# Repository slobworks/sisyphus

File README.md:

DISCLAIMER: I have not had a chance to test this out myself. I don't have any idea how or where to get an I/O bracket that would fit this consequently; I tried to make it match the one used by an ISA SB16 sound card I had on hand, but it probably is incorrect. Feel free to edit it as you see fit, in fact you have my blessing to do so.

This is the low cost (LC) variant of Sisyphus. The board is close to 1/2 the size, the headphone amp + slider and all but one 3.5" jack (the Line Output) has been removed. It still has internal Line In through a 4-pin, CD-ROM cable header, to allow for daisy-chaining sound cards within the computer.

Made in KiCAD 8.0something.
Also includes gerber files so you can try it out for yourself.

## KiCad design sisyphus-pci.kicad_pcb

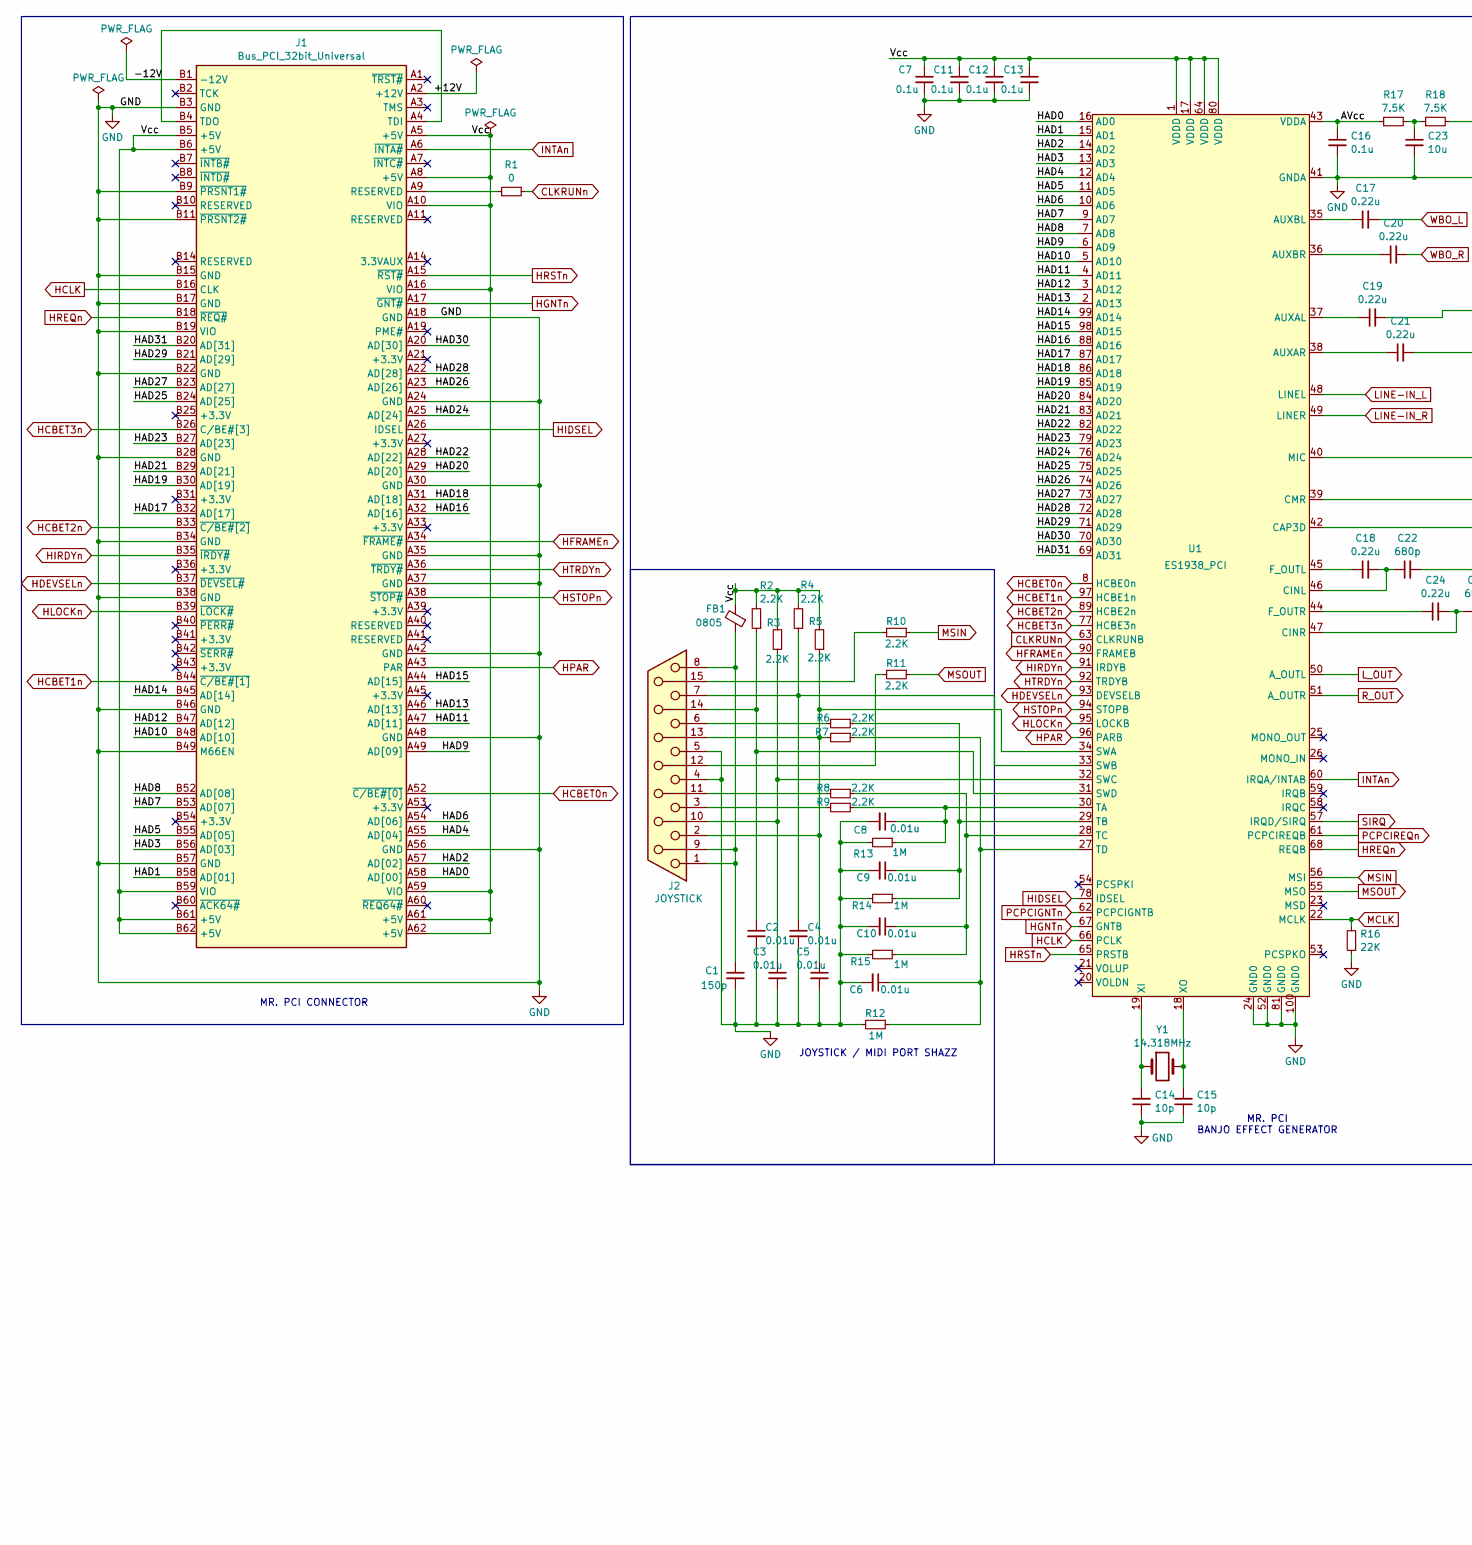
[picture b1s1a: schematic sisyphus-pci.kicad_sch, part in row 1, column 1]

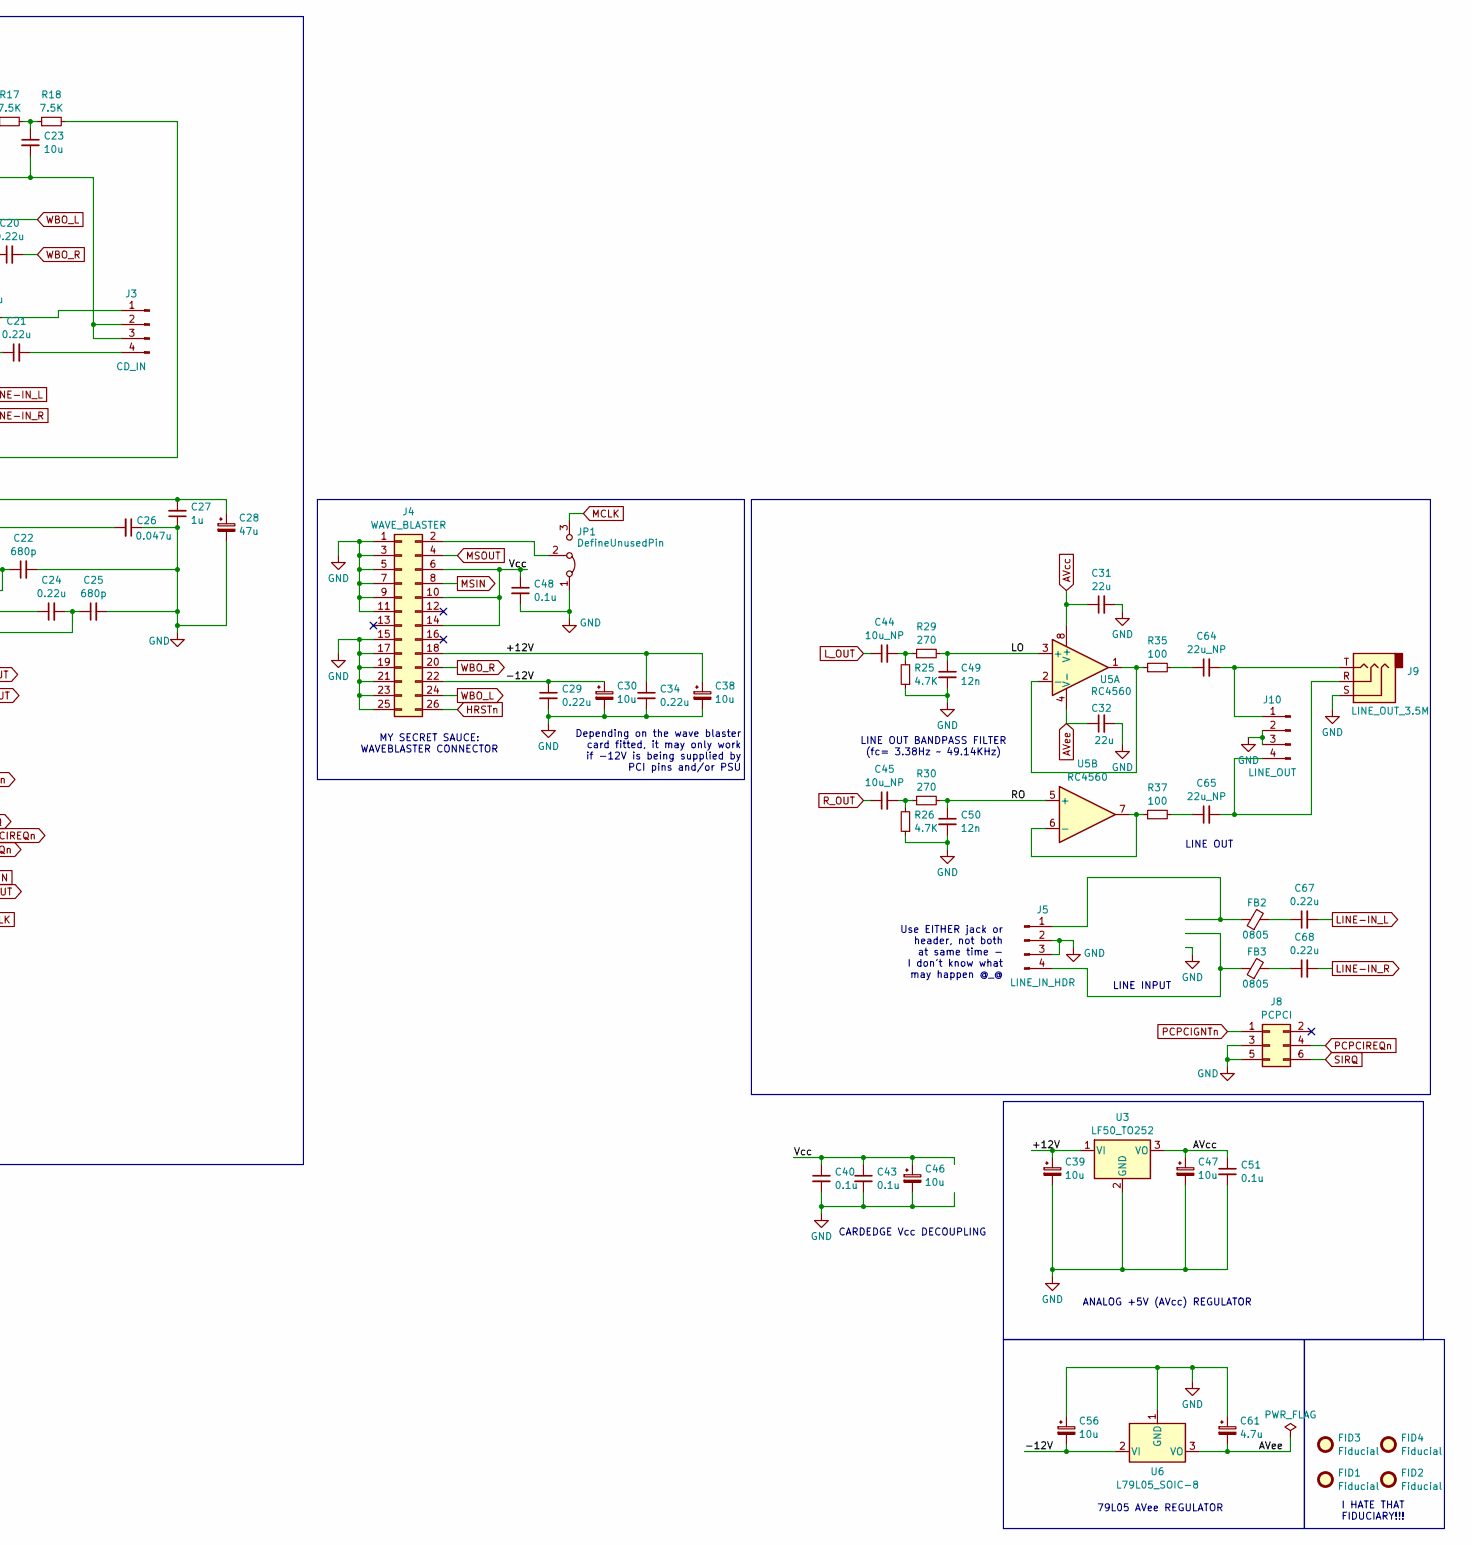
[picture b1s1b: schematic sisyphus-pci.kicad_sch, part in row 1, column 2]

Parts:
C1: 150p; C_0805_2012Metric
C2, C3, C4, C5, C6, C8, C9, C10: 0.01u; C_0805_2012Metric
C7, C11, C12, C13, C16, C40, C43, C48, C51: 0.1u; C_0805_2012Metric
C14, C15: 10p; C_0805_2012Metric
C17, C18, C19, C20, C21, C24, C29, C34, C67, C68: 0.22u; C_0805_2012Metric
C22, C25: 680p; C_0805_2012Metric
C23, C30, C38, C46, C56: 10u; C_1206_3216Metric
C26: 0.047u; C_0805_2012Metric
C27: 1u; C_0805_2012Metric
C28: 47u; C_1210_3225Metric
C31, C32: 22u; C_1206_3216Metric
C39, C47: 10u; CP_Elec_5x5.3
C44, C45: 10u_NP; CP_Radial_D5.0mm_P2.00mm
C49, C50: 12n; C_0805_2012Metric
C61: 4.7u; CP_Elec_5x5.3
C64, C65: 22u_NP; CP_Radial_D5.0mm_P2.00mm
FB1, FB2, FB3: 0805; L_0805_2012Metric
FID1, FID2, FID3, FID4: Fiducial; Fiducial_0.5mm_Mask1mm
J1: Bus_PCI_32bit_Universal; BUS_PCI
J2: JOYSTICK; DSUB-15_Female_Horizontal_P2.77x2.84mm_EdgePinOffset7.70mm_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
J3: CD_IN; PinHeader_1x04_P2.54mm_Vertical
J4: WAVE_BLASTER; PinHeader_2x13_P2.54mm_Vertical
J5: LINE_IN_HDR; PinHeader_1x04_P2.54mm_Vertical
J8: PCPCI; PinHeader_2x03_P2.54mm_Vertical
J9: LINE_OUT_3.5M; Jack_3.5mm_CUI_SJ1-3523N_Horizontal
J10: LINE_OUT; PinHeader_1x04_P2.54mm_Vertical
JP1: DefineUnusedPin; PinHeader_1x03_P1.27mm_Vertical
R1: 0; R_0805_2012Metric
R2, R3, R4, R5, R6, R7, R8, R9, R10, R11: 2.2K; R_0805_2012Metric
R12, R13, R14, R15: 1M; R_0805_2012Metric
R16: 22K; R_0805_2012Metric
R17, R18: 7.5K; R_0805_2012Metric
R25, R26: 4.7K; R_0805_2012Metric
R29, R30: 270; R_0805_2012Metric
R35, R37: 100; R_0805_2012Metric
U1: ES1938_PCI; TQFP-100_12x12mm_P0.4mm
U3: LF50_TO252; TO-252-2
U5: RC4560; SOIC-8_DMP-8
U6: L79L05_SOIC-8; SOIC-8_3.9x4.9mm_P1.27mm
Y1: 14.318MHz; Crystal_SMD_FOX_FE-2Pin_7.5x5.0mm_HandSoldering

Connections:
/+12V: C34.1, C38.1, C39.1, J1.A2 (+12V), J4.18, U3.1 (VI)
/-12V: C29.1, C30.1, C56.2, J1.B1 (-12V), J4.22, U6.2 (VI)
/HAD0: J1.A58 (AD[00]), U1.16 (AD0)
/HAD1: J1.B58 (AD[01]), U1.15 (AD1)
/HAD2: J1.A57 (AD[02]), U1.14 (AD2)
/HAD3: J1.B56 (AD[03]), U1.13 (AD3)
/HAD4: J1.A55 (AD[04]), U1.12 (AD4)
/HAD5: J1.B55 (AD[05]), U1.11 (AD5)
/HAD6: J1.A54 (AD[06]), U1.10 (AD6)
/HAD7: J1.B53 (AD[07]), U1.9 (AD7)
/HAD8: J1.B52 (AD[08]), U1.7 (AD8)
/HAD9: J1.A49 (AD[09]), U1.6 (AD9)
/HAD10: J1.B48 (AD[10]), U1.5 (AD10)
/HAD11: J1.A47 (AD[11]), U1.4 (AD11)
/HAD12: J1.B47 (AD[12]), U1.3 (AD12)
/HAD13: J1.A46 (AD[13]), U1.2 (AD13)
/HAD14: J1.B45 (AD[14]), U1.99 (AD14)
/HAD15: J1.A44 (AD[15]), U1.98 (AD15)
/HAD16: J1.A32 (AD[16]), U1.88 (AD16)
/HAD17: J1.B32 (AD[17]), U1.87 (AD17)
/HAD18: J1.A31 (AD[18]), U1.86 (AD18)
/HAD19: J1.B30 (AD[19]), U1.85 (AD19)
/HAD20: J1.A29 (AD[20]), U1.84 (AD20)
/HAD21: J1.B29 (AD[21]), U1.83 (AD21)
/HAD22: J1.A28 (AD[22]), U1.82 (AD22)
/HAD23: J1.B27 (AD[23]), U1.79 (AD23)
/HAD24: J1.A25 (AD[24]), U1.76 (AD24)
/HAD25: J1.B24 (AD[25]), U1.75 (AD25)
/HAD26: J1.A23 (AD[26]), U1.74 (AD26)
/HAD27: J1.B23 (AD[27]), U1.73 (AD27)
/HAD28: J1.A22 (AD[28]), U1.72 (AD28)
/HAD29: J1.B21 (AD[29]), U1.71 (AD29)
/HAD30: J1.A20 (AD[30]), U1.70 (AD30)
/HAD31: J1.B20 (AD[31]), U1.69 (AD31)
/LO: C49.1, R29.2, U5.3 (+)
/RO: C50.1, R30.2, U5.5 (+)
/Vcc: C7.1, C11.1, C12.1, C13.1, C40.1, C43.1, C46.1, C48.1, FB1.2, J1.A5 (+5V), J1.A8 (+5V), J1.A10 (VIO), J1.A16 (VIO), J1.A59 (VIO), J1.A61 (+5V), J1.A62 (+5V), J1.B5 (+5V), J1.B6 (+5V), J1.B59 (VIO), J1.B61 (+5V), J1.B62 (+5V), J4.6, J4.10, J4.14, R2.2, R3.2, R4.2, R5.2, U1.1 (VDDD), U1.17 (VDDD), U1.64 (VDDD), U1.80 (VDDD)
AVcc: C16.1, C31.1, C47.1, C51.1, R17.1, U1.43 (VDDA), U3.3 (VO), U5.8 (V+)
AVee: C32.1, C61.2, U5.4 (V-), U6.3 (VO)
CLKRUNn: R1.2, U1.63 (CLKRUNB)
GND: C1.2, C2.2, C3.2, C4.2, C5.2, C6.2, C7.2, C8.2, C9.2, C10.2, C11.2, C12.2, C13.2, C14.1, C15.1, C16.2, C22.2, C23.2, C25.2, C26.1, C27.1, C28.2, C29.2, C30.2, C31.2, C32.2, C34.2, C38.2, C39.2, C40.2, C43.2, C46.2, C47.2, C48.2, C49.2, C50.2, C51.2, C56.1, C61.1, J1.A18 (GND), J1.A24 (GND), J1.A30 (GND), J1.A35 (GND), J1.A37 (GND), J1.A42 (GND), J1.A48 (GND), J1.A56 (GND), J1.B3 (GND), J1.B9 (~PRSNT1#), J1.B11 (~PRSNT2#), J1.B15 (GND), J1.B17 (GND), J1.B19 (VIO), J1.B22 (GND), J1.B28 (GND), J1.B34 (GND), J1.B38 (GND), J1.B46 (GND), J1.B49 (M66EN), J1.B57 (GND), J2.4, J2.5, J3.2, J3.3, J4.1, J4.3, J4.5, J4.7, J4.9, J4.11, J4.15, J4.17, J4.19, J4.21, J4.23, J4.25, J5.2, J5.3, J8.3, J8.5, J9.S, J10.2, J10.3, JP1.1 (A), R12.2, R13.2, R14.2, R15.2, R16.1, R25.1, R26.1, U1.24 (GND0), U1.41 (GNDA), U1.52 (GND0), U1.81 (GND0), U1.100 (GND0), U3.2 (GND), U6.1 (GND)
HCBET0n: J1.A52 (~C/BE#[0]), U1.8 (HCBE0n)
HCBET1n: J1.B44 (~C/BE#[1]), U1.97 (HCBE1n)
HCBET2n: J1.B33 (~C/BE#[2]), U1.89 (HCBE2n)
HCBET3n: J1.B26 (C/BE#[3]), U1.77 (HCBE3n)
HCLK: J1.B16 (CLK), U1.66 (PCLK)
HDEVSELn: J1.B37 (~DEVSEL#), U1.93 (DEVSELB)
HFRAMEn: J1.A34 (~FRAME#), U1.90 (FRAMEB)
HGNTn: J1.A17 (~GNT#), U1.67 (GNTB)
HIDSEL: J1.A26 (IDSEL), U1.78 (IDSEL)
HIRDYn: J1.B35 (~IRDY#), U1.91 (IRDYB)
HLOCKn: J1.B39 (~LOCK#), U1.95 (LOCKB)
HPAR: J1.A43 (PAR), U1.96 (PARB)
HREQn: J1.B18 (~REQ#), U1.68 (REQB)
HRSTn: J1.A15 (~RST#), J4.26, U1.65 (PRSTB)
HSTOPn: J1.A38 (~STOP#), U1.94 (STOPB)
HTRDYn: J1.A36 (~TRDY#), U1.92 (TRDYB)
INTAn: J1.A6 (~INTA#), U1.60 (IRQA/INTAB)
LINE-IN_L: C67.2, U1.48 (LINEL)
LINE-IN_R: C68.2, U1.49 (LINER)
L_OUT: C44.1, U1.50 (A_OUTL)
MCLK: JP1.3 (B), R16.2, U1.22 (MCLK)
MSIN: J4.8, R10.1, U1.56 (MSI)
MSOUT: J4.4, R11.1, U1.55 (MSO)
unnamed: C23.1, R17.2, R18.1
unnamed: C44.2, R25.2, R29.1
unnamed: C45.2, R26.2, R30.1
unnamed: C64.1, R35.2
unnamed: C65.1, R37.2
unnamed: C67.1, FB2.2
unnamed: C68.1, FB3.2
unnamed: J1.A9 (RESERVED), R1.1
unnamed: J1.A4 (TDI), J1.B4 (TDO)
unnamed: C1.1, FB1.1, J2.1, J2.8, J2.9
unnamed: C3.1, J2.10, R3.1, U1.32 (SWC)
unnamed: J2.12, R11.2
unnamed: C5.1, J2.2, J2.13, R5.1, R7.2, U1.34 (SWA)
unnamed: C2.1, J2.14, R2.1, U1.31 (SWD)
unnamed: J2.15, R10.2
unnamed: J2.11 (P111), R8.2
unnamed: J2.3, R9.2
unnamed: J2.6, R6.2
unnamed: C19.2, J3.1
unnamed: C21.2, J3.4
unnamed: J4.2, JP1.2 (C)
unnamed: FB2.1, J5.1
unnamed: FB3.1, J5.4
unnamed: C64.2, J9.T, J10.1
unnamed: C65.2, J9.R, J10.4
unnamed: C19.1, U1.37 (AUXAL)
unnamed: C21.1, U1.38 (AUXAR)
unnamed: C17.1, U1.35 (AUXBL)
unnamed: C20.1, U1.36 (AUXBR)
unnamed: C26.2, U1.42 (CAP3D)
unnamed: C18.2, C22.1, U1.46 (CINL)
unnamed: C24.2, C25.1, U1.47 (CINR)
unnamed: C27.2, C28.1, U1.39 (CMR)
unnamed: C18.1, U1.45 (F_OUTL)
unnamed: C24.1, U1.44 (F_OUTR)
unnamed: R18.2, U1.40 (MIC)
unnamed: C4.1, J2.7, R4.1, U1.33 (SWB)
unnamed: C8.1, R9.1, R13.1, U1.30 (TA)
unnamed: C9.1, R6.1, R14.1, U1.29 (TB)
unnamed: C10.1, R8.1, R15.1, U1.28 (TC)
unnamed: C6.1, R7.1, R12.1, U1.27 (TD)
unnamed: C14.2, U1.19 (XI), Y1.1
unnamed: C15.2, U1.18 (XO), Y1.2
unnamed: R35.1, U5.1, U5.2 (-)
unnamed: R37.1, U5.6 (-), U5.7
PCPCIGNTn: J8.1, U1.62 (PCPCIGNTB)
PCPCIREQn: J8.4, U1.61 (PCPCIREQB)
R_OUT: C45.1, U1.51 (A_OUTR)
SIRQ: J8.6, U1.57 (IRQD/SIRQ)
WBO_L: C17.2, J4.24
WBO_R: C20.2, J4.20

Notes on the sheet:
JOYSTICK / MIDI PORT SHAZZ
Depending on the wave blaster card fitted, it may only work if -12V is being supplied by PCI pins and/or PSU
LINE INPUT
MY SECRET SAUCE: WAVEBLASTER CONNECTOR
ANALOG +5V (AVcc) REGULATOR
I HATE THAT FIDUCIARY!!!
LINE OUT BANDPASS FILTER (fc= 3.38Hz ~ 49.14KHz)
CARDEDGE Vcc DECOUPLING
MR. PCI BANJO EFFECT GENERATOR
79L05 AVee REGULATOR
LINE OUT
Use EITHER jack or header, not both at same time - I don't know what may happen @_@
MR. PCI CONNECTOR

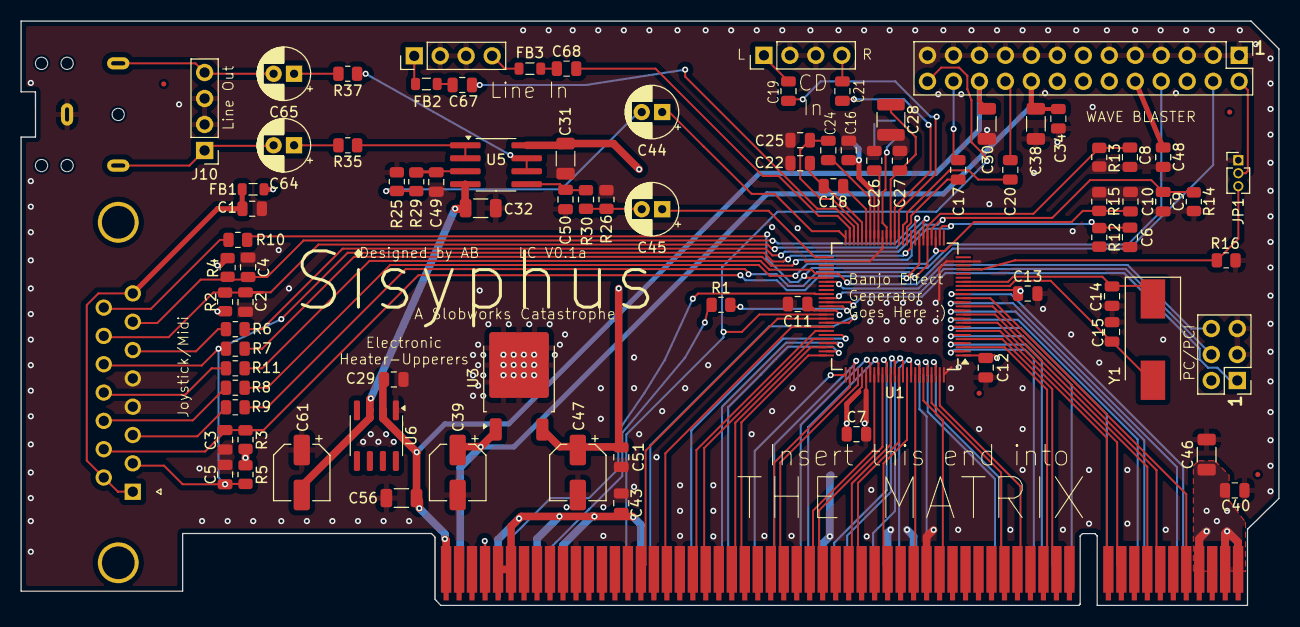
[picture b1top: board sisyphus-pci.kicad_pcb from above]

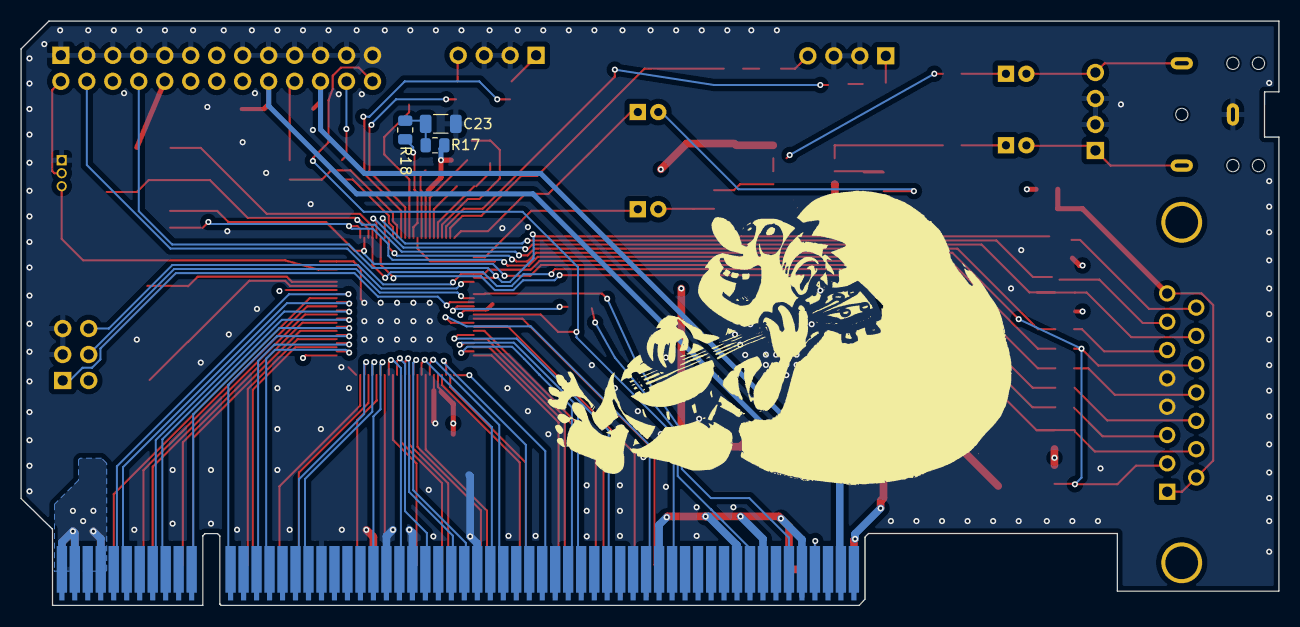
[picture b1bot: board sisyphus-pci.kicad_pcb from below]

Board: 4 copper layers, 123.0 x 57.2 mm, 96 parts (3 on the bottom side), 115 nets.

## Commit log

2024-12-05 Update README.md
    Added a picture! Ooh, look!
2024-12-07 Add files via upload
    MAJOR fixes to spacing and what not. Also made a CSV BOM.
2024-12-07 Update README.md
    Re-did picture (board has been significantly changed)
2024-12-07 Add files via upload
    Bloody hell... should be okay now.
2024-12-31 Add files via upload
    Updated to version 0.1a
2024-12-31 Add files via upload
    Smaller board. Smaller and cheaper board means better, right?
2024-12-31 Add files via upload
    Introducing the LC branch, which is a cost-reduced version with a much smaller board and reduced jacks etc.
2024-12-31 Update README.md
    Readme file for LC branch.
